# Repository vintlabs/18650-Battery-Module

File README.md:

# 18650-Battery-Module
18650 Li-Ion Battery Management Module for ESP32 Arduino Etc.

## 18650 Battery Charging/management module - Designed to be a plug-in module for ESP32-Zip DevKit, but can be used for other ESP32 modules, Arduino, etc

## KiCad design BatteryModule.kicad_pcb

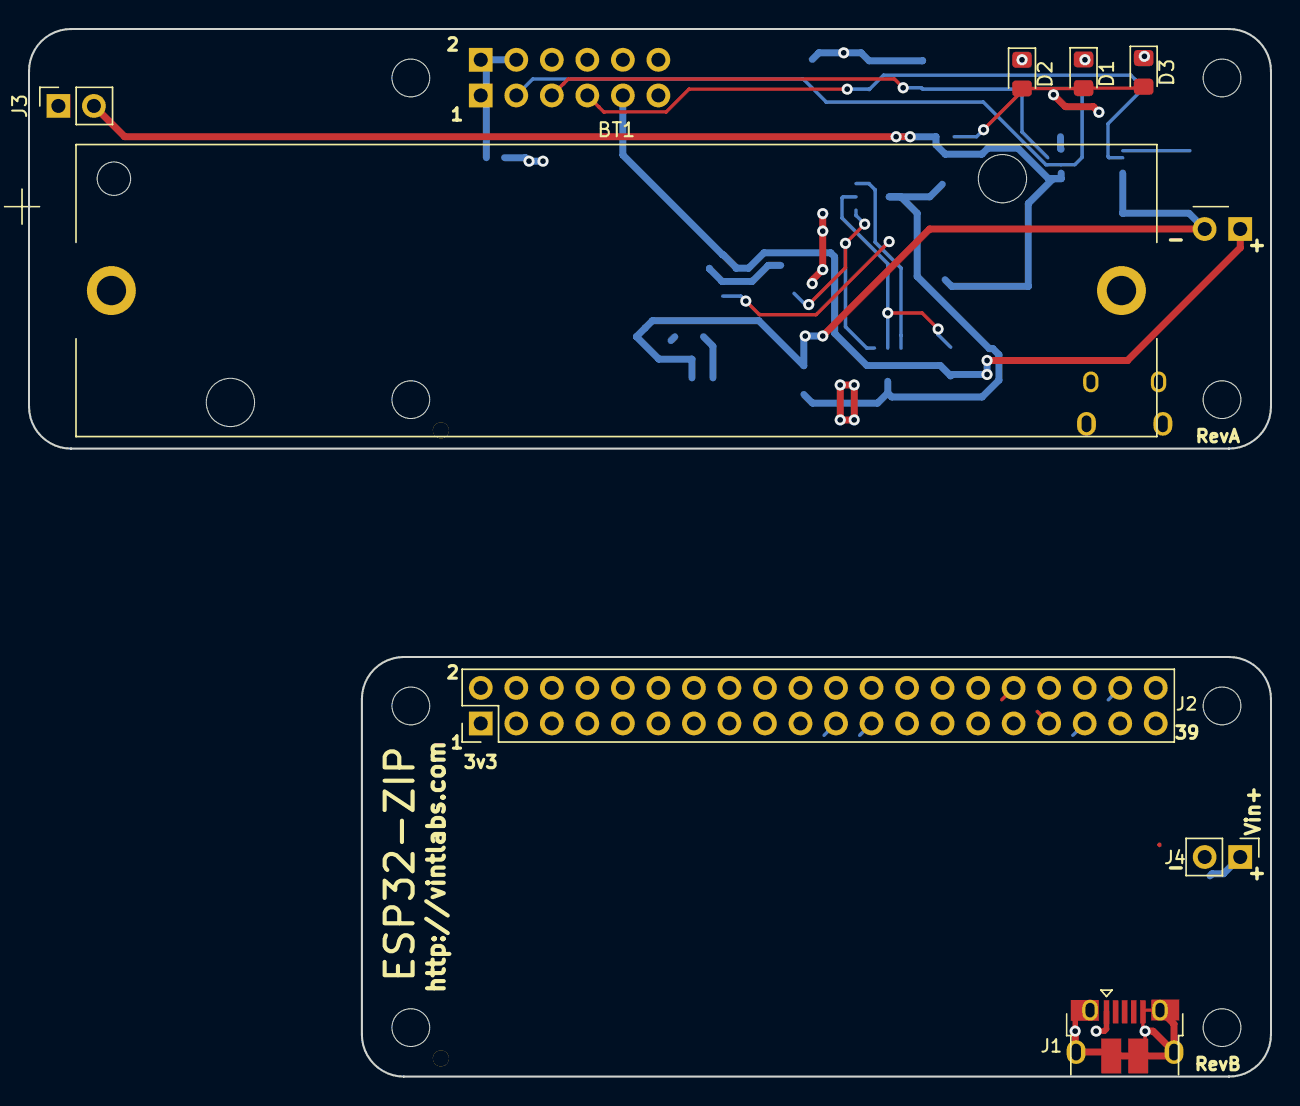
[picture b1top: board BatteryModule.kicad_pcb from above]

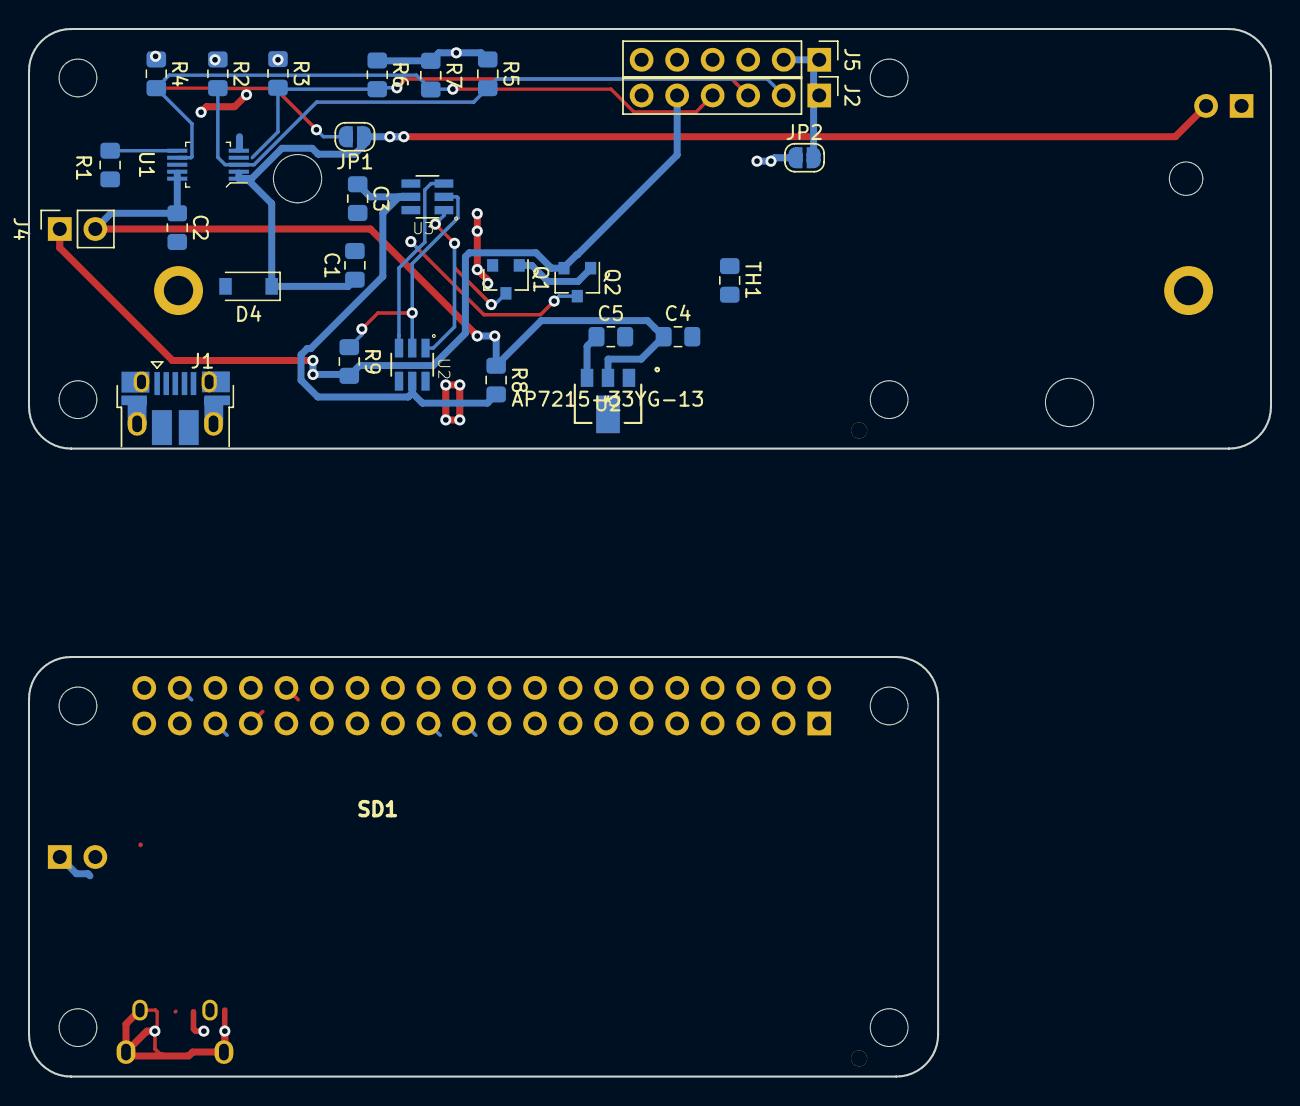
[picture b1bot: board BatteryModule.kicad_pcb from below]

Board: 2 copper layers, 88.8 x 74.9 mm, 36 parts (28 on the bottom side), 21 nets.

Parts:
BT1: Battery_Cell; BatteryHolder_Keystone_1043_1x18650
C1, C2, C4, C5: 1u; C_0805_2012Metric_Pad1.15x1.40mm_HandSolder
C3: 100nF; C_0805_2012Metric_Pad1.15x1.40mm_HandSolder
D1, D2, D3: LED; LED_0805_2012Metric_Pad1.15x1.40mm_HandSolder
D4: 1N5819HW-FDICT; D_SOD-123
J1: USB_B_Micro; USB_Micro-B_Amphenol_10118194-0001LF_Horizontal
J1#2: USB_B_Micro; USB_Micro-B_Amphenol_10103594-0001LF_Horizontal
J2: Conn_02x20_Odd_Even; PinHeader_2x20_P2.54mm_Vertical
J2#2, J5: Conn_01x06; PinHeader_1x06_P2.54mm_Vertical
J3, J4#2: Conn_01x02; PinSocket_1x02_P2.54mm_Vertical
J4: Conn_01x02_Male; PinHeader_1x02_P2.54mm_Vertical
JP1, JP2: SolderJumper_2_Open; SolderJumper-2_P1.3mm_Open_RoundedPad1.0x1.5mm
Q1, Q2: Q_NMOS_DSG; SOT-23
R1: 1k; R_0805_2012Metric_Pad1.15x1.40mm_HandSolder
R2, R3, R4: R; R_0805_2012Metric_Pad1.15x1.40mm_HandSolder
R5, R6, R7: 22k; R_0805_2012Metric_Pad1.15x1.40mm_HandSolder
R8: 330; R_0805_2012Metric_Pad1.15x1.40mm_HandSolder
R9: 2.7k; R_0805_2012Metric_Pad1.15x1.40mm_HandSolder
TH1: Thermistor_NTC; R_0805_2012Metric_Pad1.15x1.40mm_HandSolder
U1: MCP73834T-FCI/UN; MSOP-10_W3mm
U2: AP7215-33YG-13
U2#2, U3: AP9101CAK6-ANTRG1; SOT95P280X140-6N

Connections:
+3V3: C5.1, JP2.1, R5.1, R6.1, R7.1, U2.3
BATT+: BT1.1, C2.1, C4.1, J4#2.2, R8.1, U1.9, U1.10, U2.2
GND: BT1.2, C1.2, C2.2, C3.2, C4.2, C5.2, J1#2.5, J3.1, J5.3, Q1.2, R1.2, TH1.2, U1.5, U2.1, U2#2.6, U3.6
unnamed: C1.1, D4.1, J3.2, JP1.1, U1.1, U1.2
unnamed: C3.1, R8.2, U2#2.5, U3.5
unnamed: D1.1, R2.1
unnamed: D1.2, D2.2, D3.2, JP1.2
unnamed: D2.1, R3.1
unnamed: D3.1, R4.1
unnamed: D4.2, J1#2.1
unnamed: J2#2.1, J5.1, J5.2, JP2.2
unnamed: Q1.1, Q2.1
unnamed: Q1.3, U2#2.1, U3.1
unnamed: Q2.3, U2#2.3, U3.3
unnamed: R1.1, U1.6
unnamed: R9.1, U2#2.2, U3.2
unnamed: TH1.1, U1.8
P-: J2#2.5, J4#2.1, Q2.2, R9.2
PG: J2#2.4, R4.2, R7.2, U1.7
S1: J2#2.2, R2.2, R5.2, U1.3
S2: J2#2.3, R3.2, R6.2, U1.4

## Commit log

2020-01-11 Initial commit - basic concept
2020-01-11 Minor README update
2020-01-13 Basic layout done

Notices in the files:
parts and their libraries:
Copyright 2016 Accelerated Designs. All rights reserved.
